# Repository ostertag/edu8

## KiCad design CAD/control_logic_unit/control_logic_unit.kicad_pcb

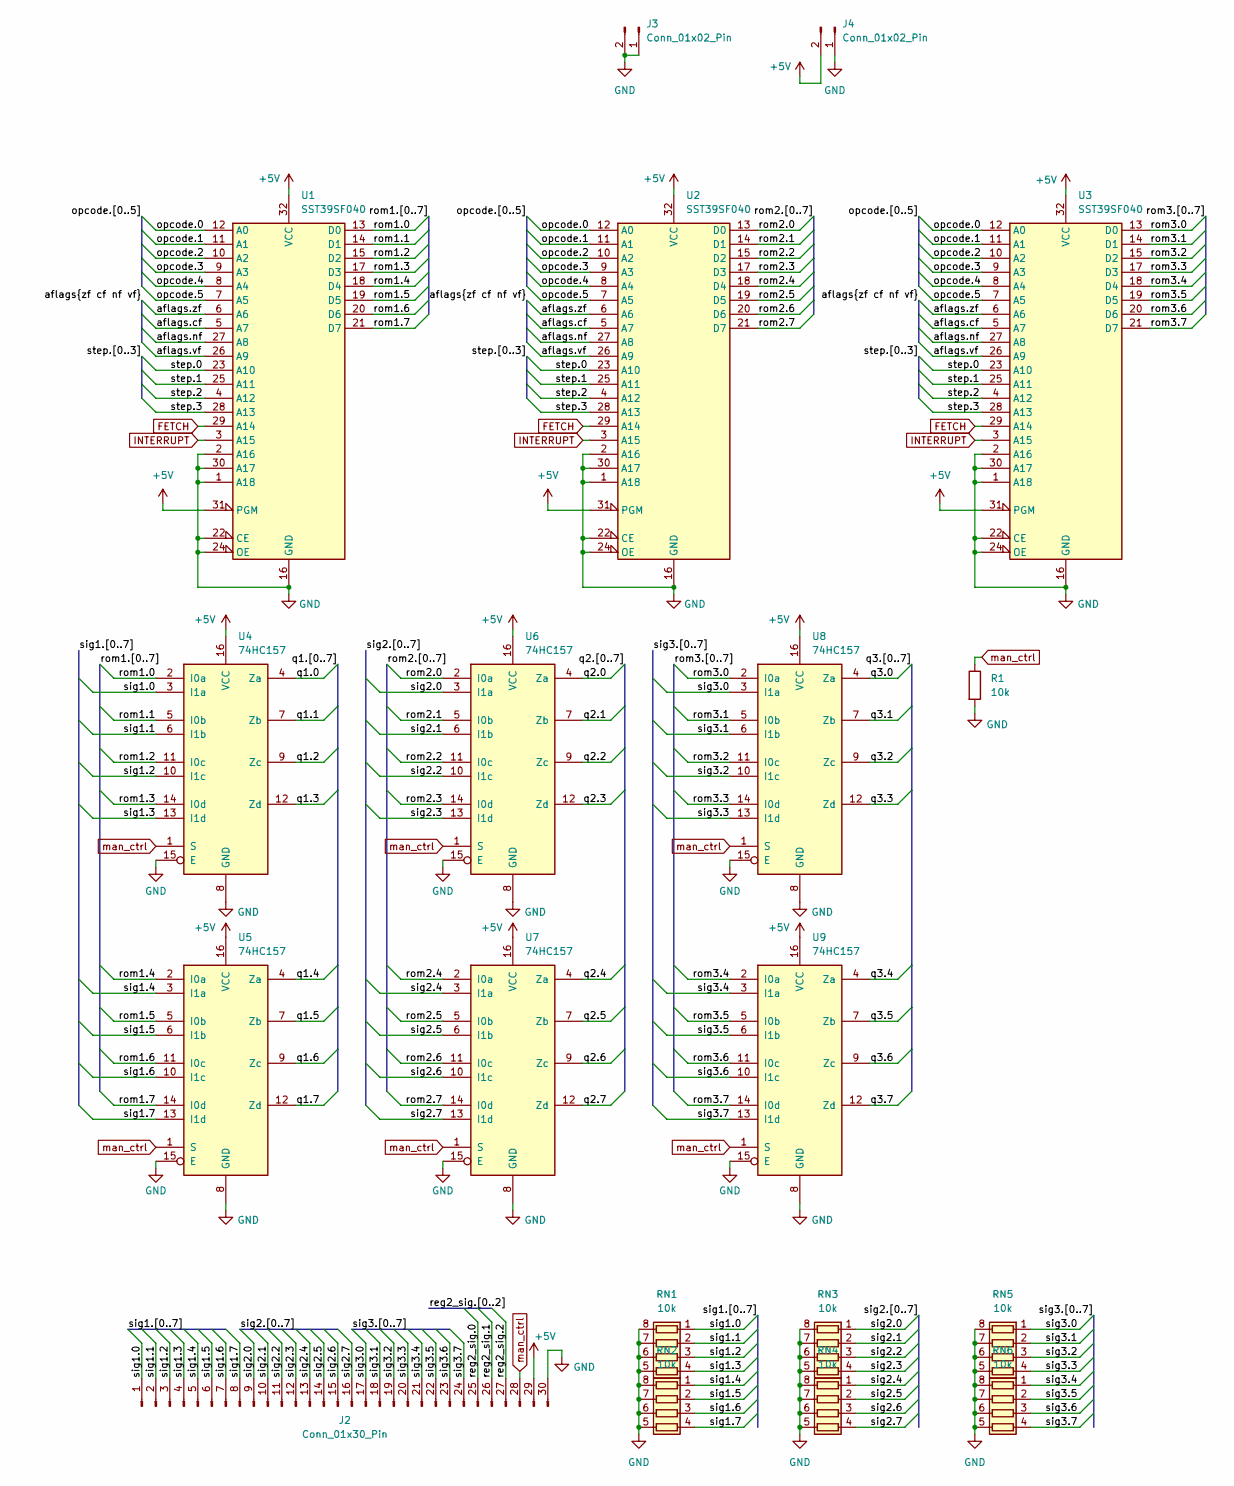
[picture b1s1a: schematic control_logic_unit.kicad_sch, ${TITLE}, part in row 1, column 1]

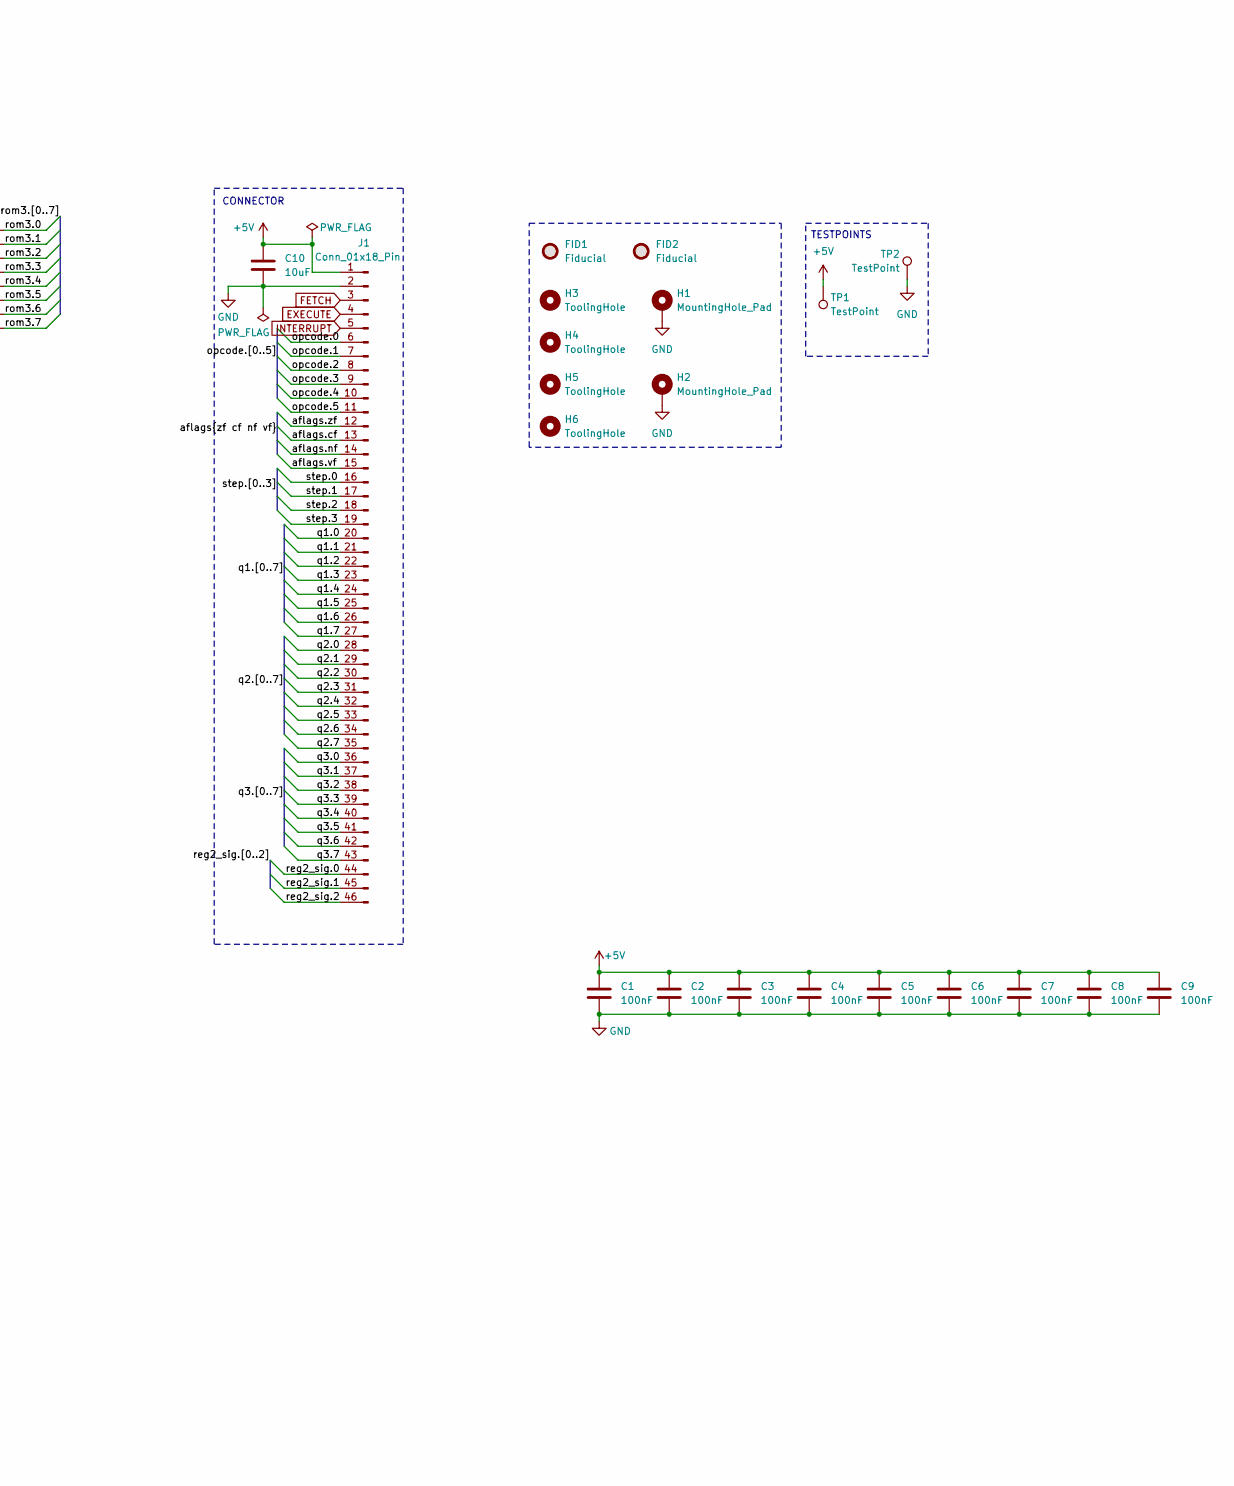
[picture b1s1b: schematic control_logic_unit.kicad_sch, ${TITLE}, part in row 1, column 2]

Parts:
C1, C2, C3, C4, C5, C6, C7, C8, C9: 100nF; C_0805_2012Metric
C10: 10uF; C_0805_2012Metric
FID1, FID2: Fiducial; Fiducial_0.5mm_Mask1mm
H1, H2: MountingHole_Pad; MountingHole_2.5mm_Pad_Via
H3, H4, H5, H6: ToolingHole; ToolingHole_1.152mm
J1: Conn_01x18_Pin; PinHeader_2x23_P2.54mm_Horizontal
J2: Conn_01x30_Pin; PinSocket_1x30_P2.54mm_Vertical
J3, J4: Conn_01x02_Pin; PinSocket_1x02_P2.54mm_Vertical
R1: 10k; R_0805_2012Metric
RN1, RN2, RN3, RN4, RN5, RN6: 10k; R_Array_Convex_4x0603
TP1, TP2: TestPoint; TestPoint_THTPad_D1.0mm_Drill0.5mm
U1, U2, U3: SST39SF040; PLCC-32_THT-Socket
U4, U5, U6, U7, U8, U9: 74HC157; SO-16_3.9x9.9mm_P1.27mm; LCSC C6823

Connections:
+5V: C1.2, C2.2, C3.2, C4.1, C5.1, C6.1, C7.1, C8.1, C9.1, C10.1, J1.1, J2.29, J4.2, TP1.1 (1_1), U1.31 (PGM), U1.32 (VCC), U2.31 (PGM), U2.32 (VCC), U3.31 (PGM), U3.32 (VCC), U4.16 (VCC), U5.16 (VCC), U6.16 (VCC), U7.16 (VCC), U8.16 (VCC), U9.16 (VCC)
/aflags.cf: J1.13, U1.5 (A7), U2.5 (A7), U3.5 (A7)
/aflags.nf: J1.14, U1.27 (A8), U2.27 (A8), U3.27 (A8)
/aflags.vf: J1.15, U1.26 (A9), U2.26 (A9), U3.26 (A9)
/aflags.zf: J1.12, U1.6 (A6), U2.6 (A6), U3.6 (A6)
/opcode.0: J1.6, U1.12 (A0), U2.12 (A0), U3.12 (A0)
/opcode.1: J1.7, U1.11 (A1), U2.11 (A1), U3.11 (A1)
/opcode.2: J1.8, U1.10 (A2), U2.10 (A2), U3.10 (A2)
/opcode.3: J1.9, U1.9 (A3), U2.9 (A3), U3.9 (A3)
/opcode.4: J1.10, U1.8 (A4), U2.8 (A4), U3.8 (A4)
/opcode.5: J1.11, U1.7 (A5), U2.7 (A5), U3.7 (A5)
/q1.0: J1.20, U4.4 (Za)
/q1.1: J1.21, U4.7 (Zb)
/q1.2: J1.22, U4.9 (Zc)
/q1.3: J1.23, U4.12 (Zd)
/q1.4: J1.24, U5.4 (Za)
/q1.5: J1.25, U5.7 (Zb)
/q1.6: J1.26, U5.9 (Zc)
/q1.7: J1.27, U5.12 (Zd)
/q2.0: J1.28, U6.4 (Za)
/q2.1: J1.29, U6.7 (Zb)
/q2.2: J1.30, U6.9 (Zc)
/q2.3: J1.31, U6.12 (Zd)
/q2.4: J1.32, U7.4 (Za)
/q2.5: J1.33, U7.7 (Zb)
/q2.6: J1.34, U7.9 (Zc)
/q2.7: J1.35, U7.12 (Zd)
/q3.0: J1.36, U8.4 (Za)
/q3.1: J1.37, U8.7 (Zb)
/q3.2: J1.38, U8.9 (Zc)
/q3.3: J1.39, U8.12 (Zd)
/q3.4: J1.40, U9.4 (Za)
/q3.5: J1.41, U9.7 (Zb)
/q3.6: J1.42, U9.9 (Zc)
/q3.7: J1.43, U9.12 (Zd)
/reg2_sig.0: J1.44, J2.25
/reg2_sig.1: J1.45, J2.26
/reg2_sig.2: J1.46, J2.27
/rom1.0: U1.13 (D0), U4.2 (I0a)
/rom1.1: U1.14 (D1), U4.5 (I0b)
/rom1.2: U1.15 (D2), U4.11 (I0c)
/rom1.3: U1.17 (D3), U4.14 (I0d)
/rom1.4: U1.18 (D4), U5.2 (I0a)
/rom1.5: U1.19 (D5), U5.5 (I0b)
/rom1.6: U1.20 (D6), U5.11 (I0c)
/rom1.7: U1.21 (D7), U5.14 (I0d)
/rom2.0: U2.13 (D0), U6.2 (I0a)
/rom2.1: U2.14 (D1), U6.5 (I0b)
/rom2.2: U2.15 (D2), U6.11 (I0c)
/rom2.3: U2.17 (D3), U6.14 (I0d)
/rom2.4: U2.18 (D4), U7.2 (I0a)
/rom2.5: U2.19 (D5), U7.5 (I0b)
/rom2.6: U2.20 (D6), U7.11 (I0c)
/rom2.7: U2.21 (D7), U7.14 (I0d)
/rom3.0: U3.13 (D0), U8.2 (I0a)
/rom3.1: U3.14 (D1), U8.5 (I0b)
/rom3.2: U3.15 (D2), U8.11 (I0c)
/rom3.3: U3.17 (D3), U8.14 (I0d)
/rom3.4: U3.18 (D4), U9.2 (I0a)
/rom3.5: U3.19 (D5), U9.5 (I0b)
/rom3.6: U3.20 (D6), U9.11 (I0c)
/rom3.7: U3.21 (D7), U9.14 (I0d)
/sig1.0: J2.1, RN1.1 (R1.1), U4.3 (I1a)
/sig1.1: J2.2, RN1.2 (R2.1), U4.6 (I1b)
/sig1.2: J2.3, RN1.3 (R3.1), U4.10 (I1c)
/sig1.3: J2.4, RN1.4 (R4.1), U4.13 (I1d)
/sig1.4: J2.5, RN2.1 (R1.1), U5.3 (I1a)
/sig1.5: J2.6, RN2.2 (R2.1), U5.6 (I1b)
/sig1.6: J2.7, RN2.3 (R3.1), U5.10 (I1c)
/sig1.7: J2.8, RN2.4 (R4.1), U5.13 (I1d)
/sig2.0: J2.9, RN3.1 (R1.1), U6.3 (I1a)
/sig2.1: J2.10, RN3.2 (R2.1), U6.6 (I1b)
/sig2.2: J2.11, RN3.3 (R3.1), U6.10 (I1c)
/sig2.3: J2.12, RN3.4 (R4.1), U6.13 (I1d)
/sig2.4: J2.13, RN4.1 (R1.1), U7.3 (I1a)
/sig2.5: J2.14, RN4.2 (R2.1), U7.6 (I1b)
/sig2.6: J2.15, RN4.3 (R3.1), U7.10 (I1c)
/sig2.7: J2.16, RN4.4 (R4.1), U7.13 (I1d)
/sig3.0: J2.17, RN5.1 (R1.1), U8.3 (I1a)
/sig3.1: J2.18, RN5.2 (R2.1), U8.6 (I1b)
/sig3.2: J2.19, RN5.3 (R3.1), U8.10 (I1c)
/sig3.3: J2.20, RN5.4 (R4.1), U8.13 (I1d)
/sig3.4: J2.21, RN6.1 (R1.1), U9.3 (I1a)
/sig3.5: J2.22, RN6.2 (R2.1), U9.6 (I1b)
/sig3.6: J2.23, RN6.3 (R3.1), U9.10 (I1c)
/sig3.7: J2.24, RN6.4 (R4.1), U9.13 (I1d)
/step.0: J1.16, U1.23 (A10), U2.23 (A10), U3.23 (A10)
/step.1: J1.17, U1.25 (A11), U2.25 (A11), U3.25 (A11)
/step.2: J1.18, U1.4 (A12), U2.4 (A12), U3.4 (A12)
/step.3: J1.19, U1.28 (A13), U2.28 (A13), U3.28 (A13)
EXECUTE: J1.4
FETCH: J1.3, U1.29 (A14), U2.29 (A14), U3.29 (A14)
GND: C1.1, C2.1, C3.1, C4.2, C5.2, C6.2, C7.2, C8.2, C9.2, C10.2, H1.1 (1_1), H2.1 (1_1), J1.2, J2.30, J3.1, J3.2, J4.1, R1.2, RN1.5 (R4.2), RN1.6 (R3.2), RN1.7 (R2.2), RN1.8 (R1.2), RN2.5 (R4.2), RN2.6 (R3.2), RN2.7 (R2.2), RN2.8 (R1.2), RN3.5 (R4.2), RN3.6 (R3.2), RN3.7 (R2.2), RN3.8 (R1.2), RN4.5 (R4.2), RN4.6 (R3.2), RN4.7 (R2.2), RN4.8 (R1.2), RN5.5 (R4.2), RN5.6 (R3.2), RN5.7 (R2.2), RN5.8 (R1.2), RN6.5 (R4.2), RN6.6 (R3.2), RN6.7 (R2.2), RN6.8 (R1.2), TP2.1 (1_1), U1.1 (A18), U1.2 (A16), U1.16 (GND), U1.22 (CE), U1.24 (OE), U1.30 (A17), U2.1 (A18), U2.2 (A16), U2.16 (GND), U2.22 (CE), U2.24 (OE), U2.30 (A17), U3.1 (A18), U3.2 (A16), U3.16 (GND), U3.22 (CE), U3.24 (OE), U3.30 (A17), U4.8 (GND), U4.15 (E), U5.8 (GND), U5.15 (E), U6.8 (GND), U6.15 (E), U7.8 (GND), U7.15 (E), U8.8 (GND), U8.15 (E), U9.8 (GND), U9.15 (E)
INTERRUPT: J1.5, U1.3 (A15), U2.3 (A15), U3.3 (A15)
man_ctrl: J2.28, R1.1, U4.1 (S), U5.1 (S), U6.1 (S), U7.1 (S), U8.1 (S), U9.1 (S)

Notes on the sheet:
TESTPOINTS
CONNECTOR

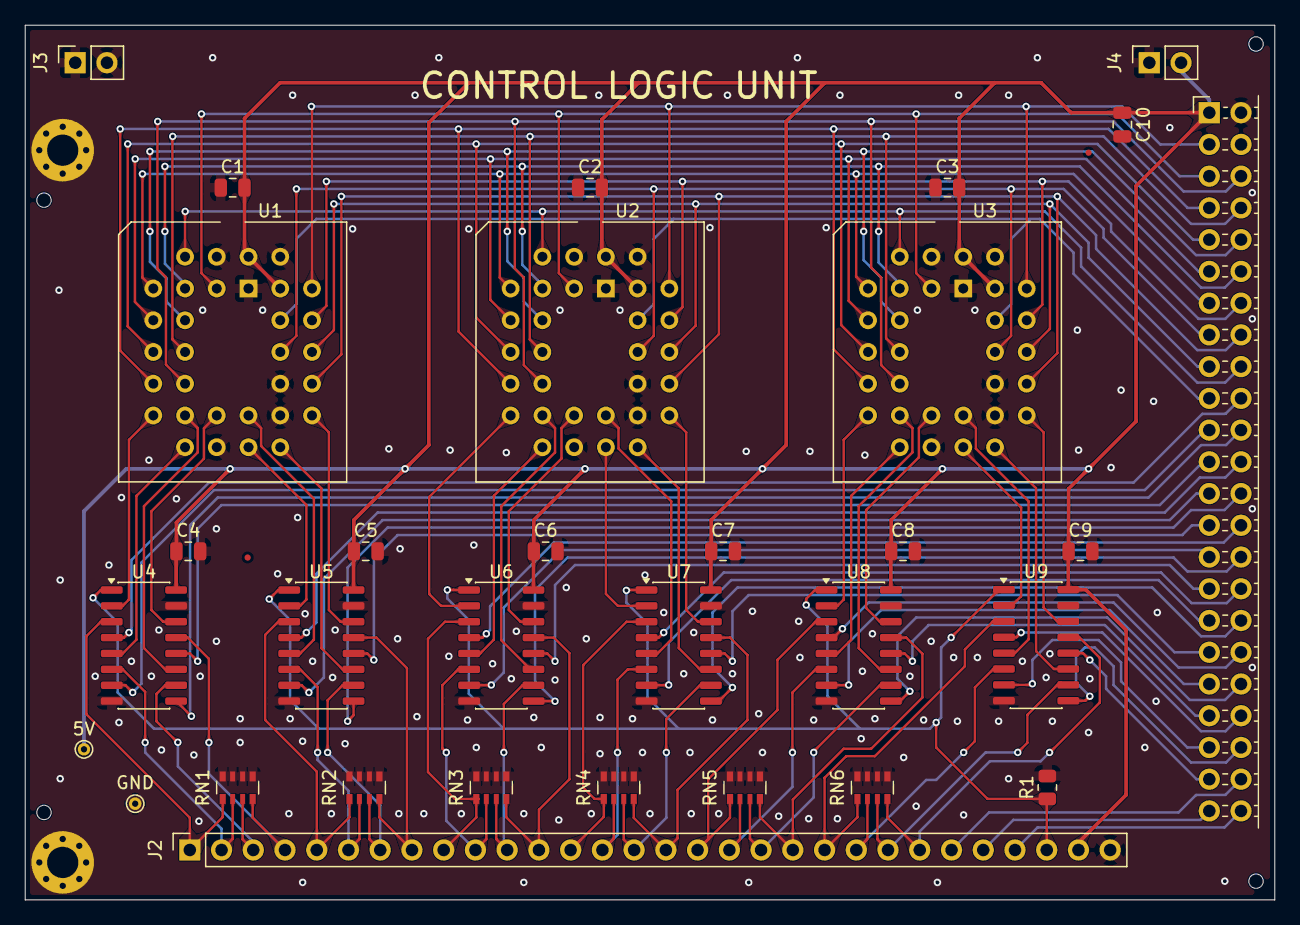
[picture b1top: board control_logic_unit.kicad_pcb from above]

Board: 2 copper layers, 100.0 x 70.0 mm, 41 parts (1 on the bottom side), 94 nets.

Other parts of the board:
Ref**: Val**; by-nc-sa.eu

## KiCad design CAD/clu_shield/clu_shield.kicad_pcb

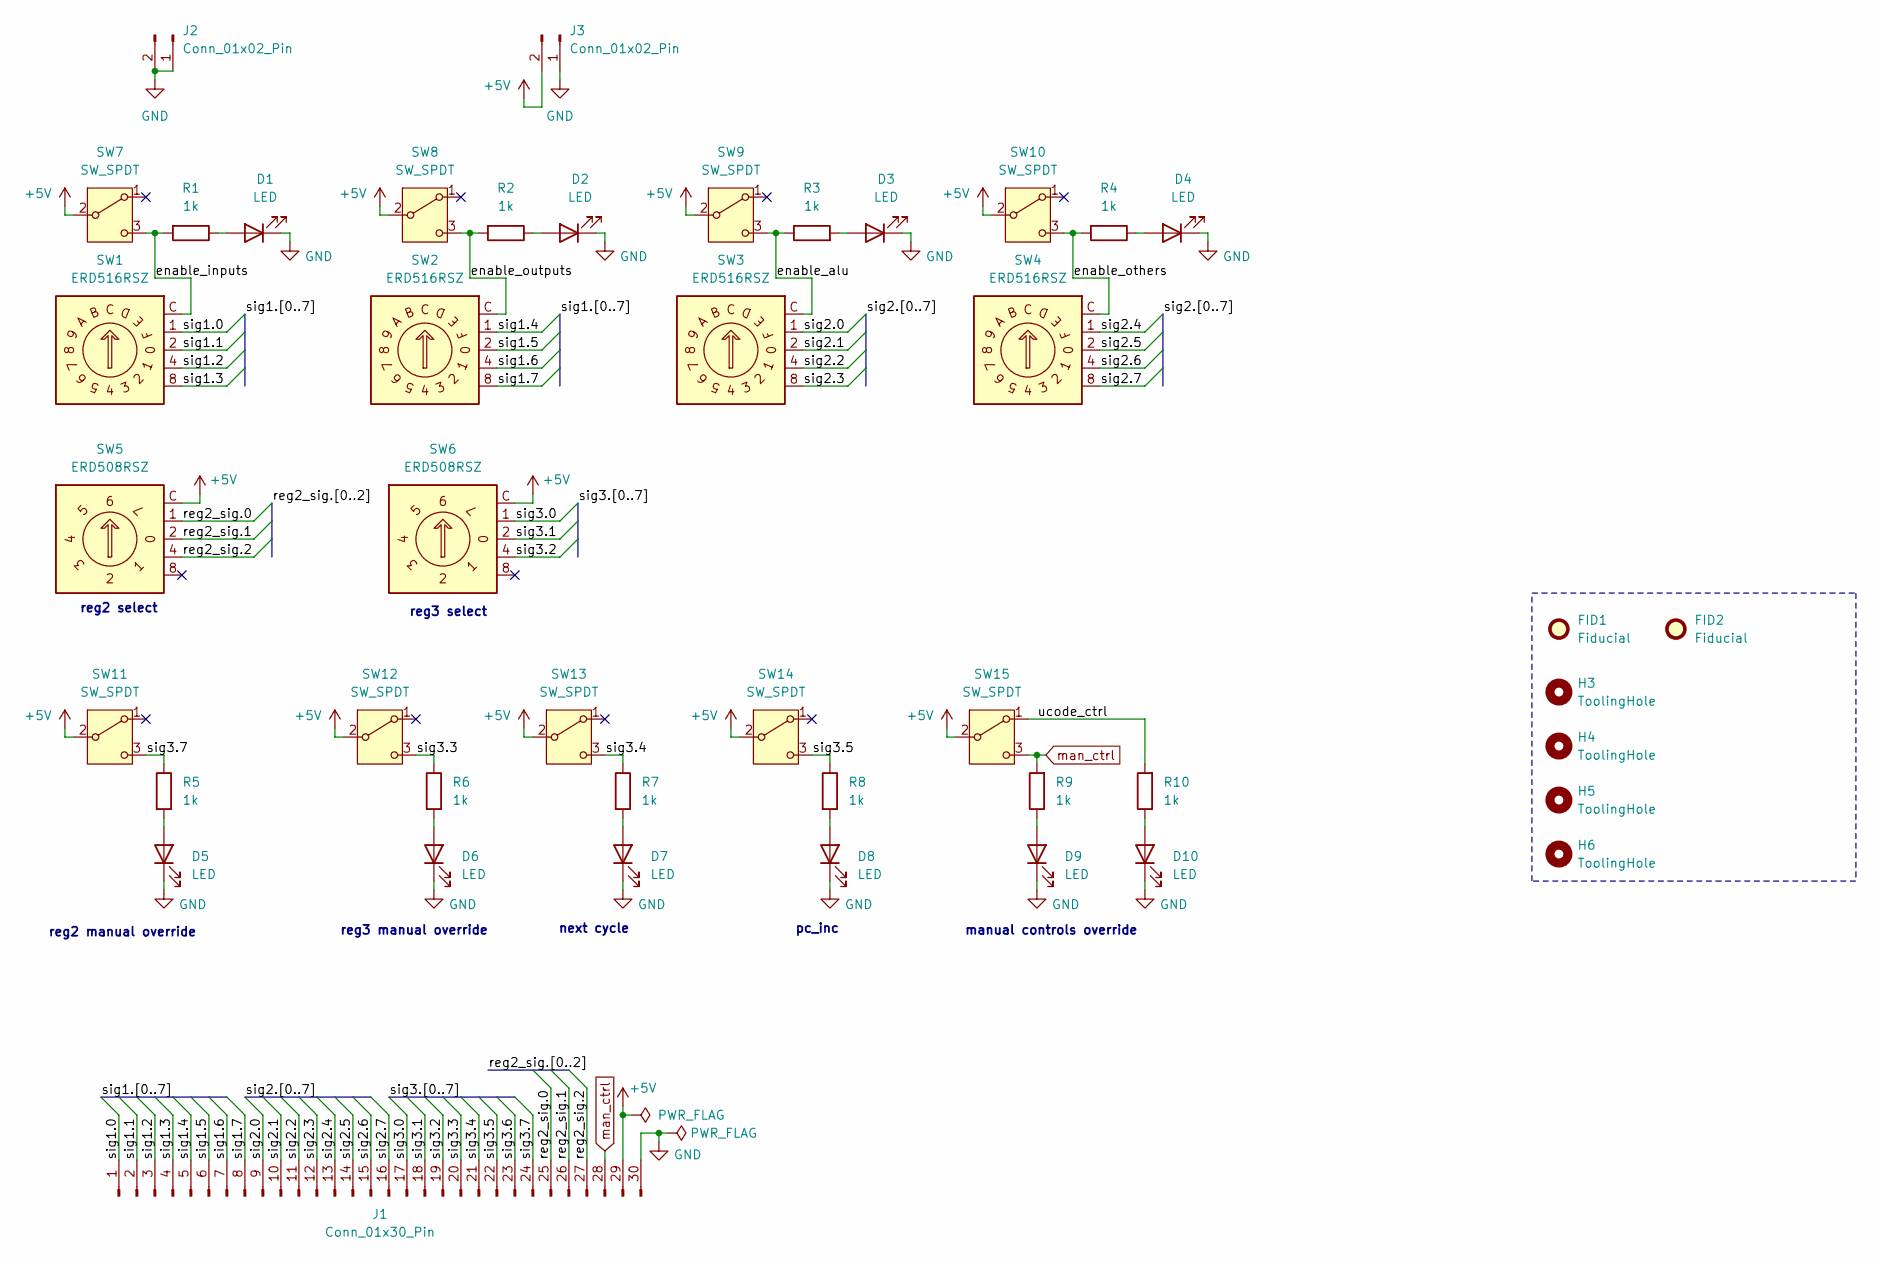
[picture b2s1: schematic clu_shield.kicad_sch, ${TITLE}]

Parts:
D1, D2, D3, D4, D5, D6, D7, D8, D9, D10: LED; LED_0805_2012Metric
FID1, FID2: Fiducial; Fiducial_0.5mm_Mask1mm
H3, H4, H5, H6: ToolingHole; ToolingHole_1.152mm
J1: Conn_01x30_Pin; PinHeader_1x30_P2.54mm_Vertical
J2, J3: Conn_01x02_Pin; PinHeader_1x02_P2.54mm_Vertical
R1, R2, R3, R4, R5, R6, R7, R8, R9, R10: 1k; R_0805_2012Metric
SW1, SW2, SW3, SW4: ERD516RSZ; ERD5XXXS
SW5, SW6: ERD508RSZ; ERD5XXXS
SW7, SW8, SW9, SW10, SW11, SW12, SW13, SW14, SW15: SW_SPDT; SW_Slide_SPDT_8.5x3.8mm

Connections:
+5V: J1.29, J3.2, SW5.C, SW6.C, SW7.2 (B), SW8.2 (B), SW9.2 (B), SW10.2 (B), SW11.2 (B), SW12.2 (B), SW13.2 (B), SW14.2 (B), SW15.2 (B)
/enable_alu: R3.1, SW3.C, SW9.3 (C)
/enable_inputs: R1.2, SW1.C, SW7.3 (C)
/enable_others: R4.2, SW4.C, SW10.3 (C)
/enable_outputs: R2.2, SW2.C, SW8.3 (C)
/reg2_sig.0: J1.25, SW5.1
/reg2_sig.1: J1.26, SW5.2
/reg2_sig.2: J1.27, SW5.4
/sig1.0: J1.1, SW1.1
/sig1.1: J1.2, SW1.2
/sig1.2: J1.3, SW1.4
/sig1.3: J1.4, SW1.8
/sig1.4: J1.5, SW2.1
/sig1.5: J1.6, SW2.2
/sig1.6: J1.7, SW2.4
/sig1.7: J1.8, SW2.8
/sig2.0: J1.9, SW3.1
/sig2.1: J1.10, SW3.2
/sig2.2: J1.11, SW3.4
/sig2.3: J1.12, SW3.8
/sig2.4: J1.13, SW4.1
/sig2.5: J1.14, SW4.2
/sig2.6: J1.15, SW4.4
/sig2.7: J1.16, SW4.8
/sig3.0: J1.17, SW6.1
/sig3.1: J1.18, SW6.2
/sig3.2: J1.19, SW6.4
/sig3.3: J1.20, R6.1, SW12.3 (C)
/sig3.4: J1.21, R7.1, SW13.3 (C)
/sig3.5: J1.22, R8.1, SW14.3 (C)
/sig3.6: J1.23
/sig3.7: J1.24, R5.1, SW11.3 (C)
/ucode_ctrl: R10.2, SW15.1 (A)
GND: D1.1 (K), D2.1 (K), D3.1 (K), D4.1 (K), D5.1 (K), D6.1 (K), D7.1 (K), D8.1 (K), D9.1 (K), D10.1 (K), J1.30, J2.1, J2.2, J3.1
unnamed: D1.2 (A), R1.1
unnamed: D2.2 (A), R2.1
unnamed: D3.2 (A), R3.2
unnamed: D4.2 (A), R4.1
unnamed: D5.2 (A), R5.2
unnamed: D6.2 (A), R6.2
unnamed: D7.2 (A), R7.2
unnamed: D8.2 (A), R8.2
unnamed: D9.2 (A), R9.1
unnamed: D10.2 (A), R10.1
man_ctrl: J1.28, R9.2, SW15.3 (C)

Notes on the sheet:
next cycle
reg2 select
reg3 select
pc_inc
manual controls override
reg2 manual override
reg3 manual override

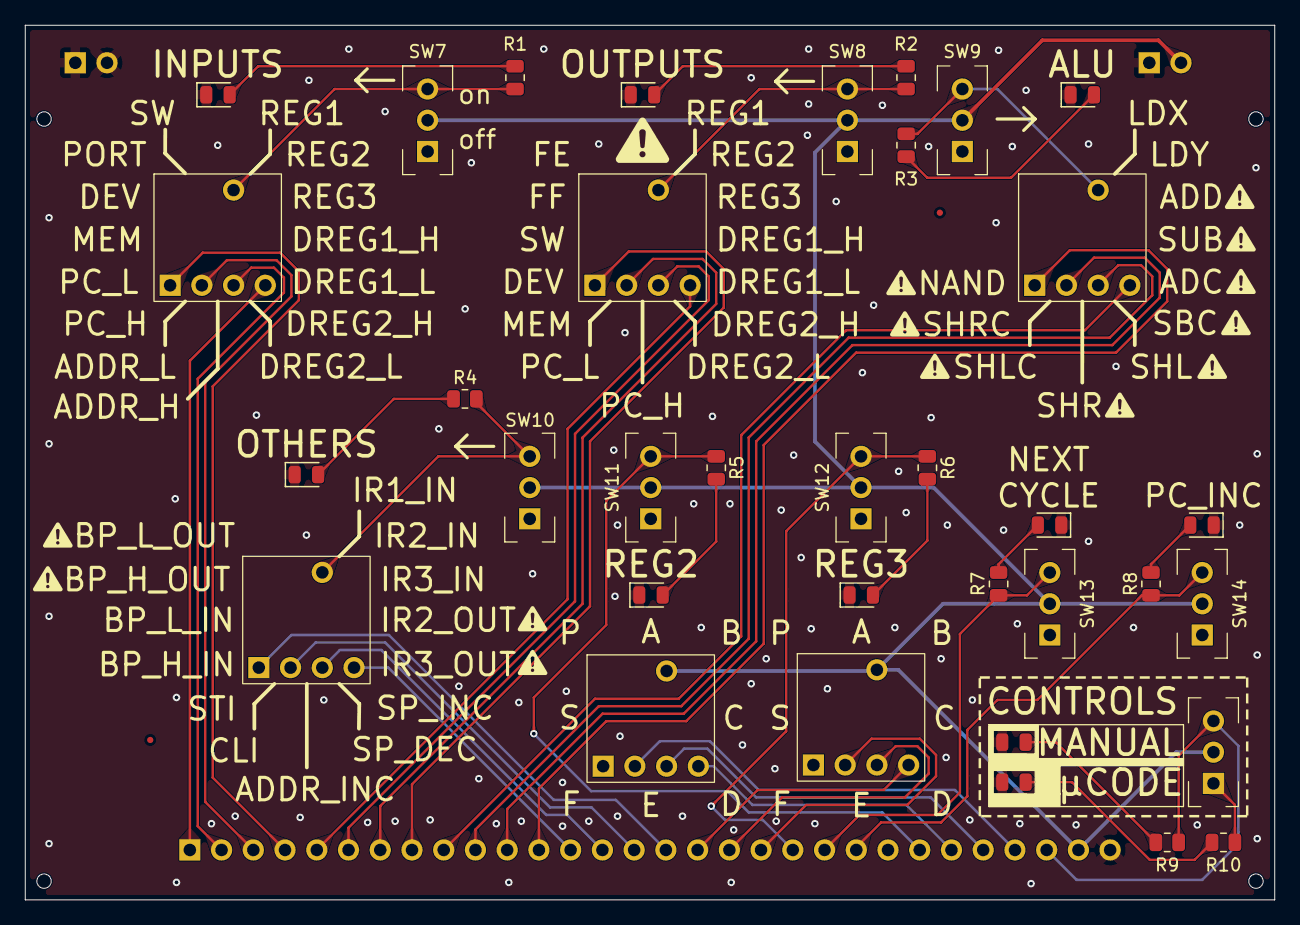
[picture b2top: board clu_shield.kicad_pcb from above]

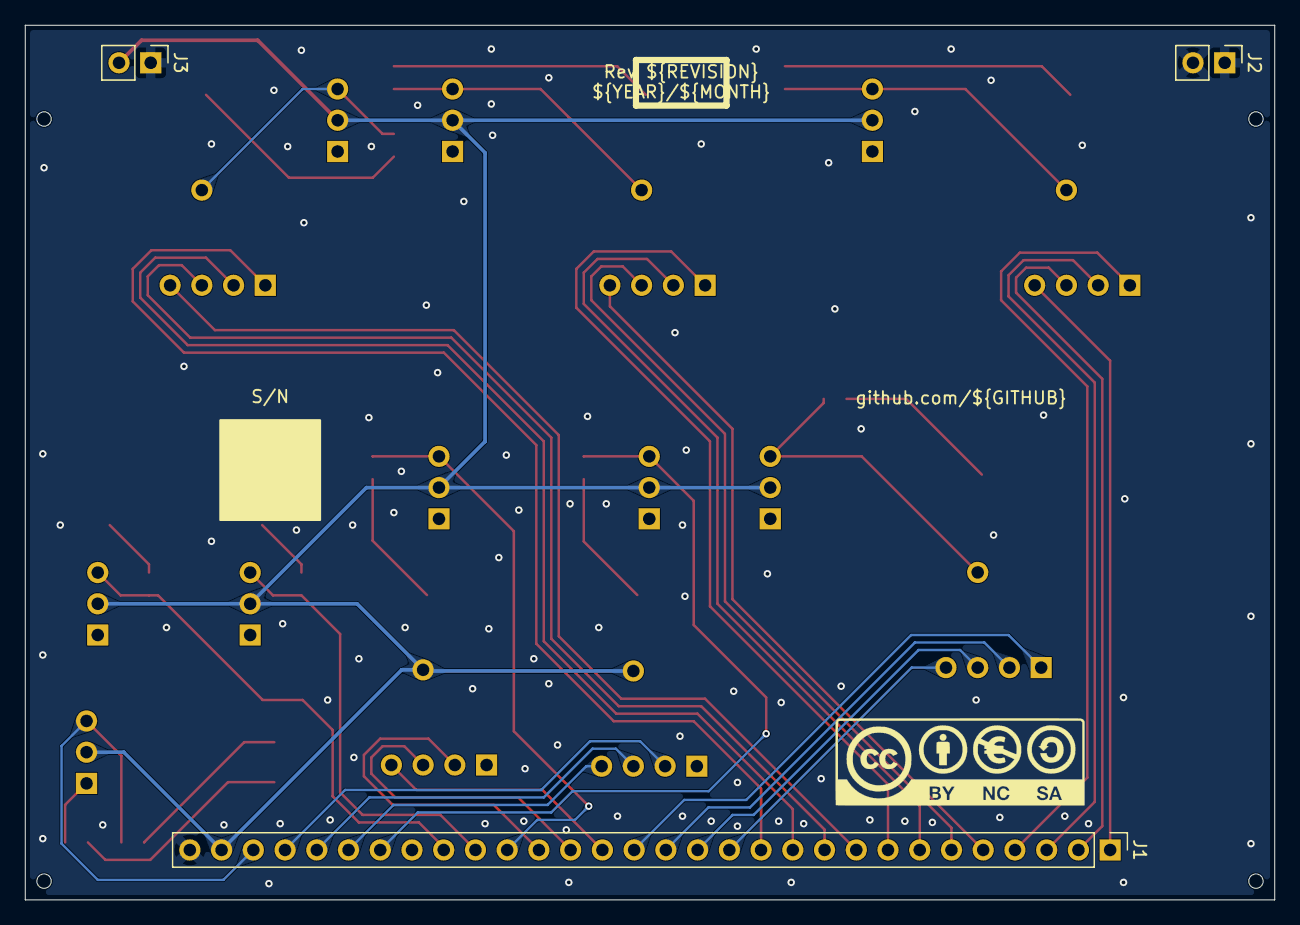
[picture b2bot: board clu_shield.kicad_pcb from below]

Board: 2 copper layers, 100.0 x 70.0 mm, 45 parts (4 on the bottom side), 44 nets.

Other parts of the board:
Ref**: Val**; by-nc-sa.eu

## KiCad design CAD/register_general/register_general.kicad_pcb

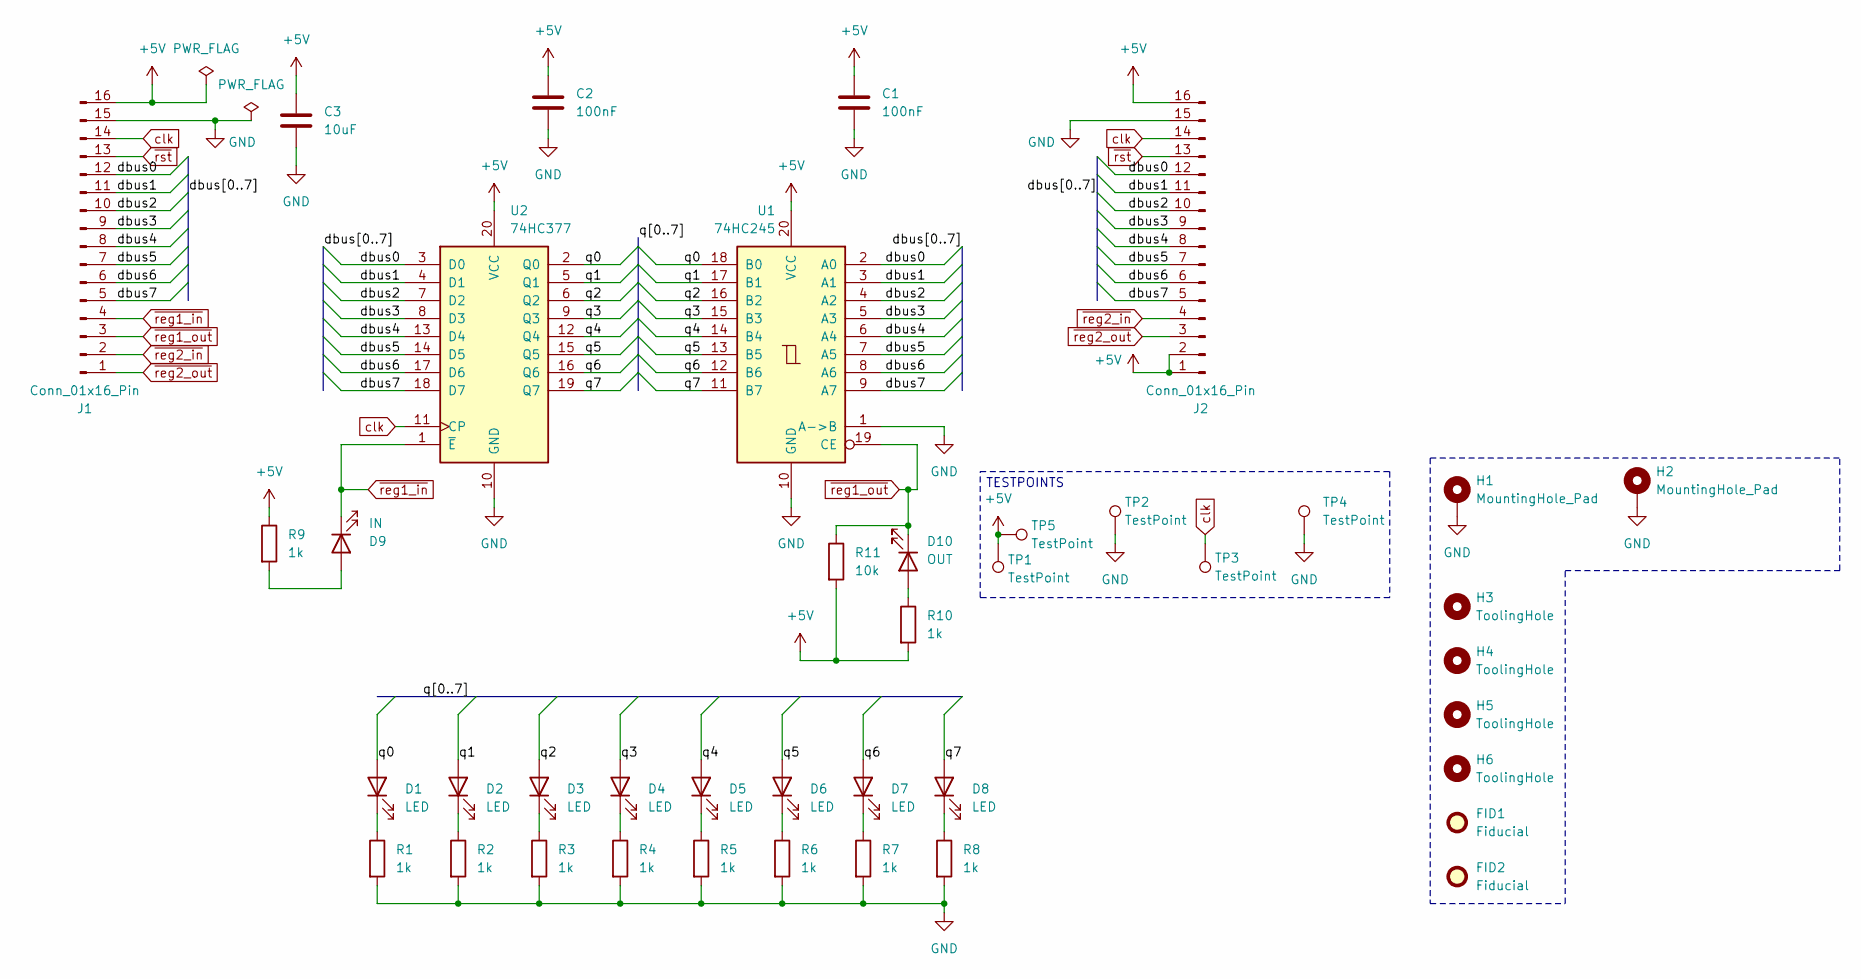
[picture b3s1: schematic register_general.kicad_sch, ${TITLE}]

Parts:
C1, C2: 100nF; C_0805_2012Metric; LCSC C28233
C3: 10uF; C_0805_2012Metric; LCSC C15850
D1, D2, D3, D4, D5, D6, D7, D8: LED; LED_0805_2012Metric; LCSC C84256
D9: IN; LED_0805_2012Metric; LCSC C2297
D10: OUT; LED_0805_2012Metric; LCSC C2296
FID1, FID2: Fiducial; Fiducial_0.5mm_Mask1mm
H1, H2: MountingHole_Pad; MountingHole_2.5mm_Pad_Via
H3, H4, H5, H6: ToolingHole; ToolingHole_1.152mm
J1: Conn_01x16_Pin; PinHeader_2x08_P2.54mm_Horizontal; LCSC C492436
J2: Conn_01x16_Pin; PinSocket_2x08_P2.54mm_Horizontal; LCSC C22465965
R1, R2, R3, R4, R5, R6, R7, R8, R9, R10: 1k; R_0805_2012Metric; LCSC C17513
R11: 10k; R_0805_2012Metric; LCSC C17414
TP1, TP2, TP3, TP4: TestPoint; TestPoint_THTPad_D1.0mm_Drill0.5mm
TP5: TestPoint; TestPoint_Slot_2.2x0.8mm
U1: 74HC245; SOIC-20W_7.5x12.8mm_P1.27mm; LCSC C5625
U2: 74HC377; SO-20_5.3x12.6mm_P1.27mm; LCSC C7647

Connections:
+5V: C1.1, C2.1, C3.1, J1.16, J2.1, J2.2, J2.16, R9.1, R10.2, R11.2, TP1.1 (1_1), TP5.1 (1_1), U1.20 (VCC), U2.20 (VCC)
/dbus0: J1.12, J2.12, U1.2 (A0), U2.3 (D0)
/dbus1: J1.11, J2.11, U1.3 (A1), U2.4 (D1)
/dbus2: J1.10, J2.10, U1.4 (A2), U2.7 (D2)
/dbus3: J1.9, J2.9, U1.5 (A3), U2.8 (D3)
/dbus4: J1.8, J2.8, U1.6 (A4), U2.13 (D4)
/dbus5: J1.7, J2.7, U1.7 (A5), U2.14 (D5)
/dbus6: J1.6, J2.6, U1.8 (A6), U2.17 (D6)
/dbus7: J1.5, J2.5, U1.9 (A7), U2.18 (D7)
/q0: D1.2 (A), U1.18 (B0), U2.2 (Q0)
/q1: D2.2 (A), U1.17 (B1), U2.5 (Q1)
/q2: D3.2 (A), U1.16 (B2), U2.6 (Q2)
/q3: D4.2 (A), U1.15 (B3), U2.9 (Q3)
/q4: D5.2 (A), U1.14 (B4), U2.12 (Q4)
/q5: D6.2 (A), U1.13 (B5), U2.15 (Q5)
/q6: D7.2 (A), U1.12 (B6), U2.16 (Q6)
/q7: D8.2 (A), U1.11 (B7), U2.19 (Q7)
GND: C1.2, C2.2, C3.2, H1.1 (1_1), H2.1 (1_1), J1.15, J2.15, R1.2, R2.2, R3.2, R4.2, R5.2, R6.2, R7.2, R8.2, TP2.1 (1_1), TP4.1 (1_1), U1.1 (A->B), U1.10 (GND), U2.10 (GND)
unnamed: D1.1 (K), R1.1
unnamed: D2.1 (K), R2.1
unnamed: D3.1 (K), R3.1
unnamed: D4.1 (K), R4.1
unnamed: D5.1 (K), R5.1
unnamed: D6.1 (K), R6.1
unnamed: D7.1 (K), R7.1
unnamed: D8.1 (K), R8.1
unnamed: D9.2 (A), R9.2
unnamed: D10.2 (A), R10.1
clk: J1.14, J2.14, TP3.1 (1_1), U2.11 (CP)
~reg1_in: D9.1 (K), J1.4, U2.1 (~E)
~reg1_out: D10.1 (K), J1.3, R11.1, U1.19 (CE)
~reg2_in: J1.2, J2.4
~reg2_out: J1.1, J2.3
~rst: J1.13, J2.13

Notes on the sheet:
TESTPOINTS

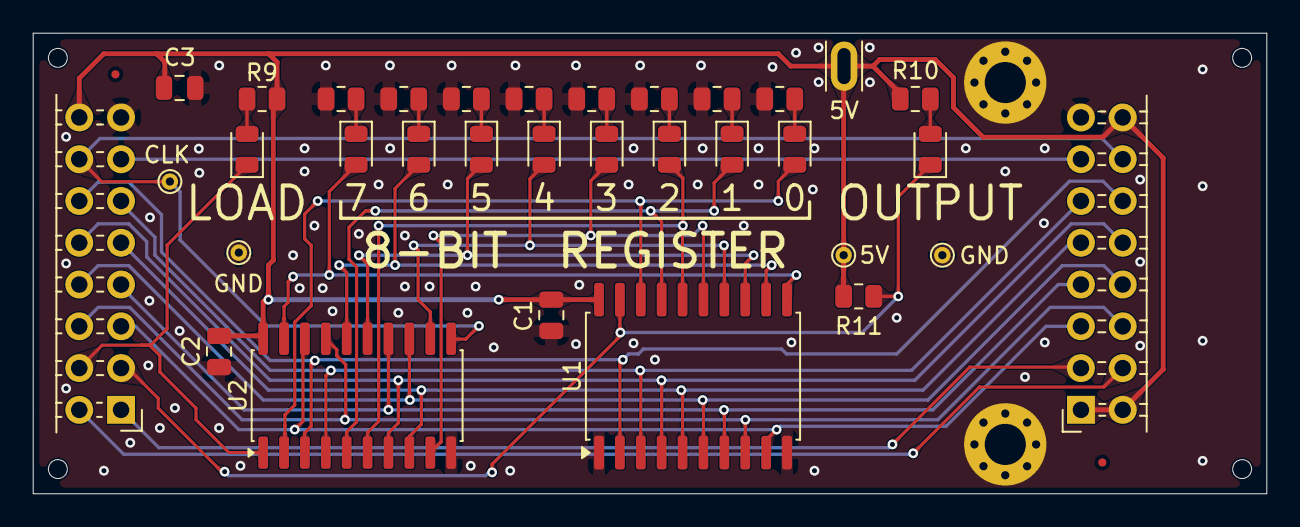
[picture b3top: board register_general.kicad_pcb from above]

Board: 2 copper layers, 75.0 x 28.0 mm, 42 parts (1 on the bottom side), 34 nets.

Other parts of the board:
Ref**: Val**; by-nc-sa.eu
